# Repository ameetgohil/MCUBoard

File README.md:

# MCUBoard
STM32F104 board with LEDs
<br />
## MCUBoard 3D View

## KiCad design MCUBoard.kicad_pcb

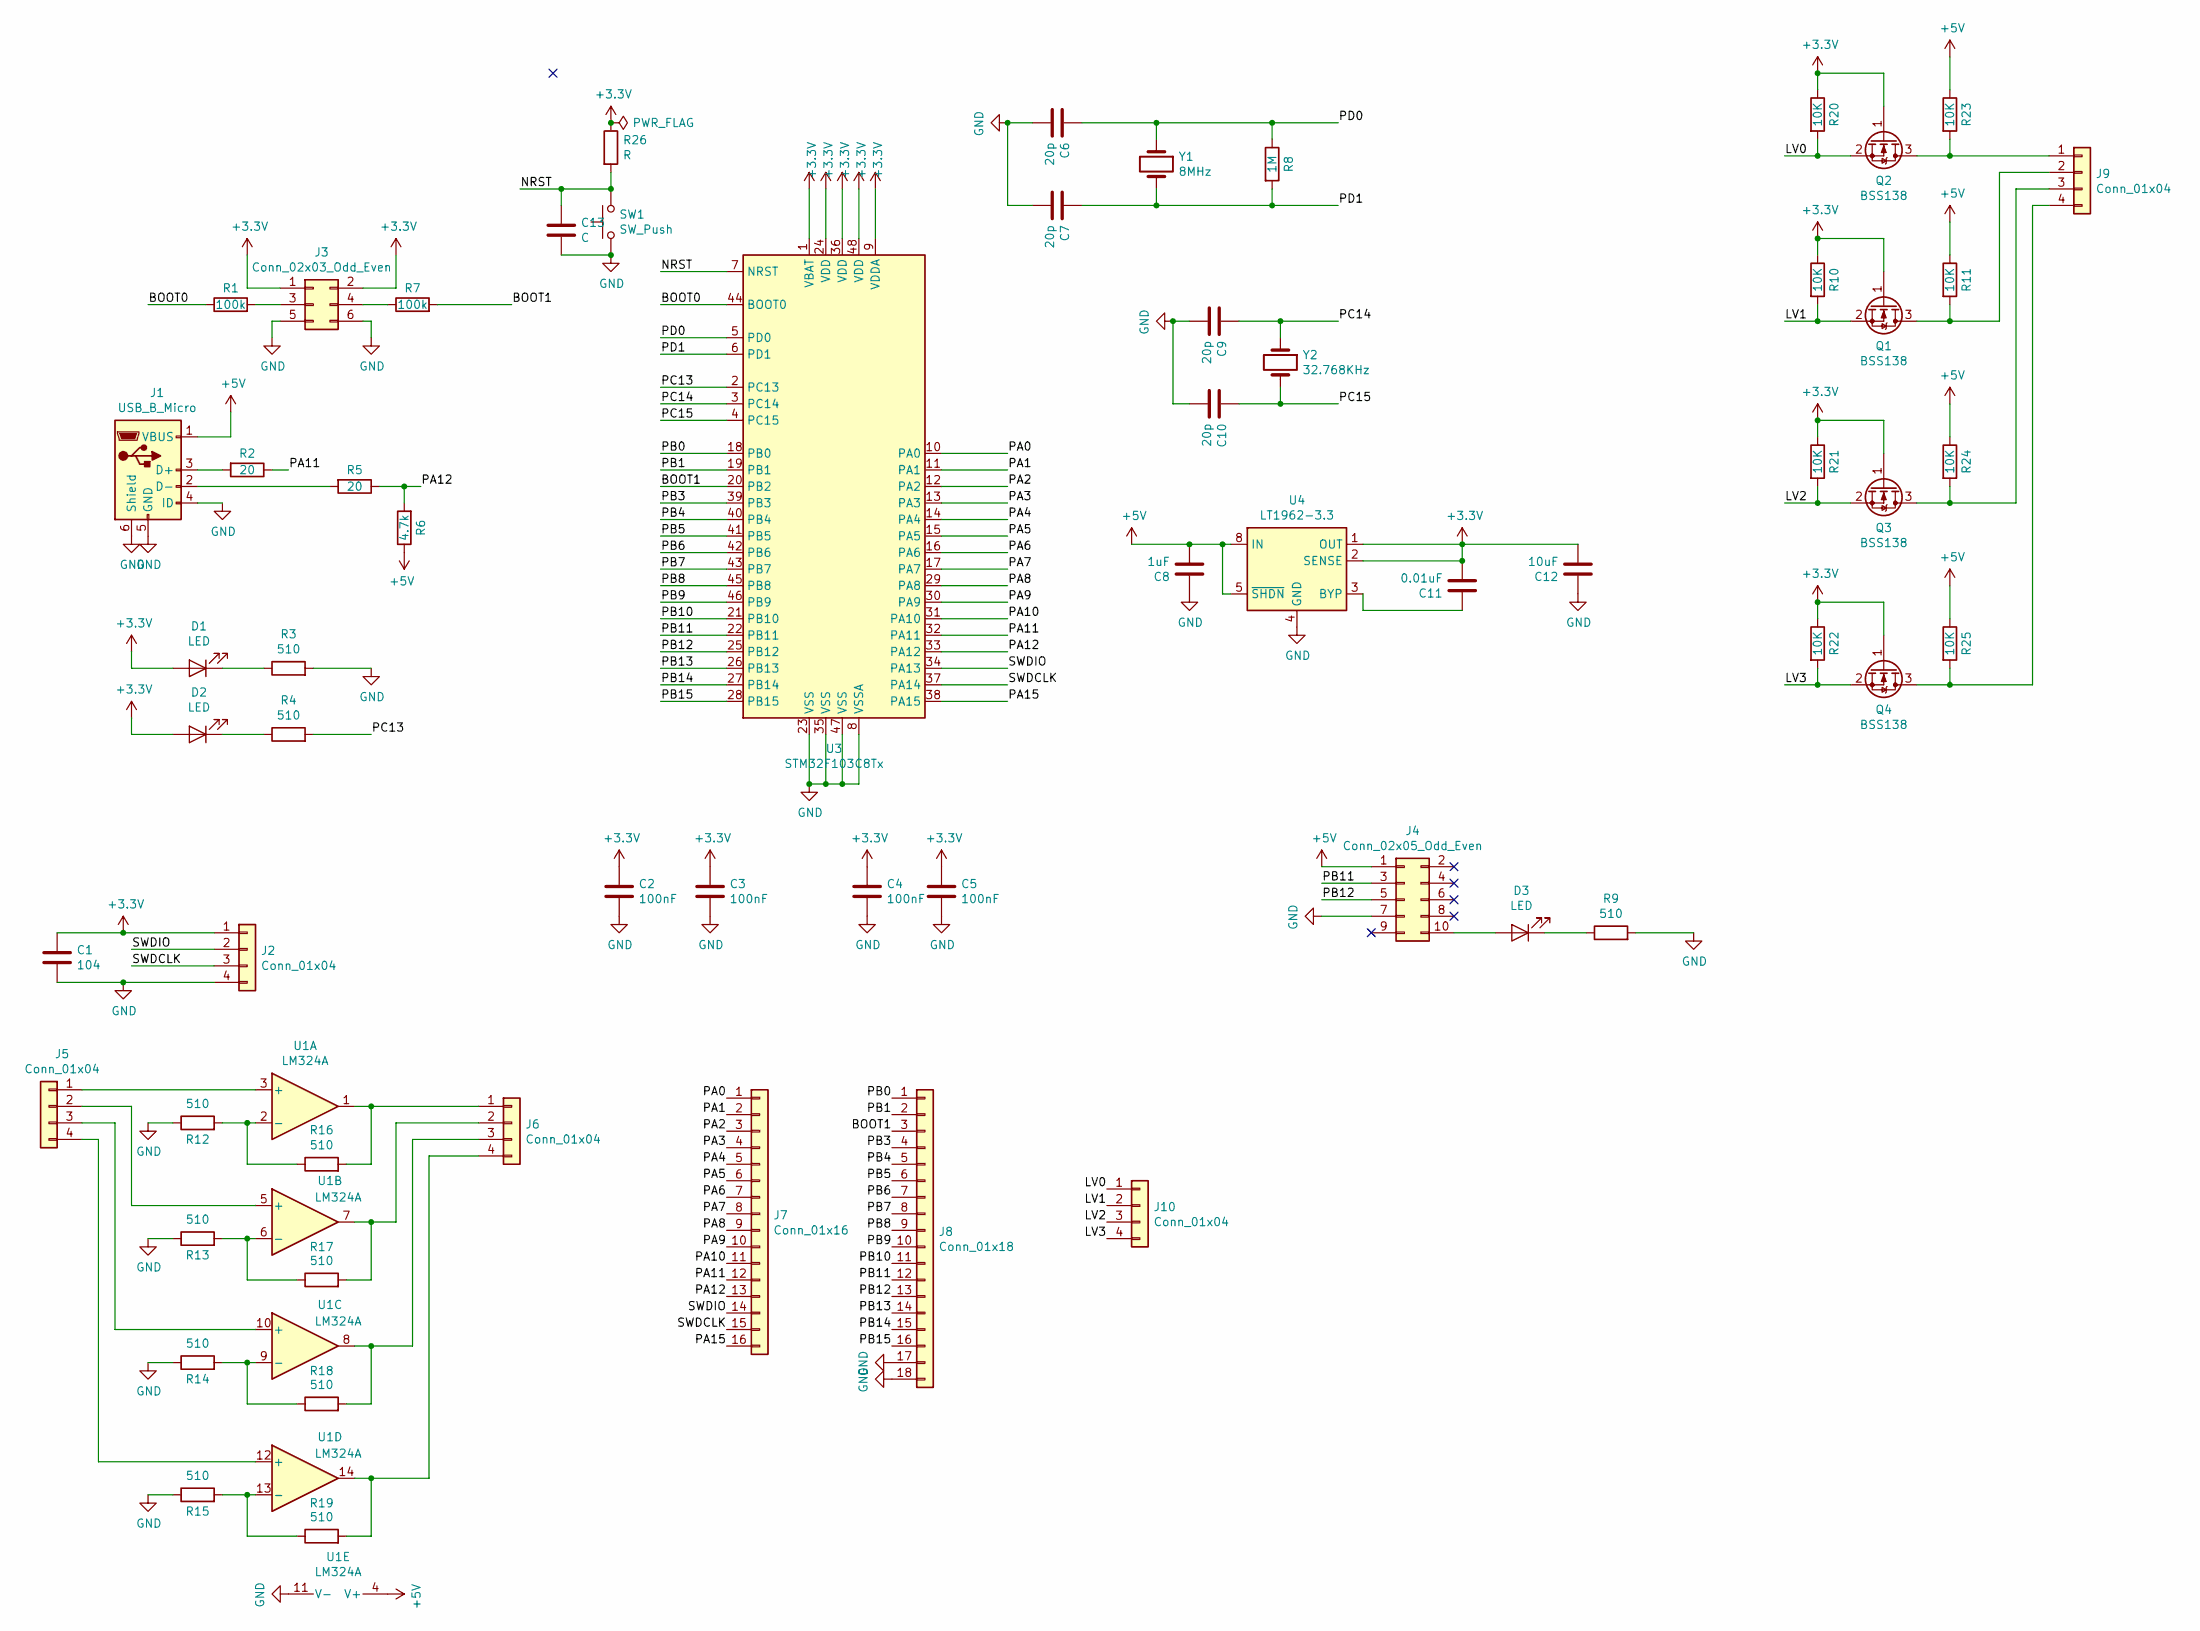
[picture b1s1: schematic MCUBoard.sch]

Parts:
C1: 104; C_1806_4516Metric_Pad1.57x1.80mm_HandSolder
C2, C3, C4, C5: 100nF; C_1806_4516Metric_Pad1.57x1.80mm_HandSolder
C6, C7, C9, C10: 20p; C_1806_4516Metric_Pad1.57x1.80mm_HandSolder
C8: 1uF; C_1806_4516Metric_Pad1.57x1.80mm_HandSolder
C11: 0.01uF; C_1806_4516Metric_Pad1.57x1.80mm_HandSolder
C12: 10uF; C_1806_4516Metric_Pad1.57x1.80mm_HandSolder
C13: C; C_1806_4516Metric_Pad1.57x1.80mm_HandSolder
D1, D2, D3: LED; LED_1206_3216Metric_Pad1.42x1.75mm_HandSolder
J1: USB_B_Micro; USB_Micro-B_Molex_47346-0001
J2, J5, J6, J9, J10: Conn_01x04; PinHeader_1x04_P2.54mm_Vertical
J3: Conn_02x03_Odd_Even; PinHeader_2x03_P2.54mm_Vertical
J4: Conn_02x05_Odd_Even; PinHeader_2x05_P2.54mm_Vertical
J7: Conn_01x16; PinHeader_1x16_P2.54mm_Vertical
J8: Conn_01x18; PinHeader_1x18_P2.54mm_Vertical
Q1, Q2, Q3, Q4: BSS138; SOT-23_Handsoldering
R1, R7: 100k; R_1806_4516Metric_Pad1.57x1.80mm_HandSolder
R2, R5: 20; R_1806_4516Metric_Pad1.57x1.80mm_HandSolder
R3, R4, R9, R12, R13, R14, R15, R16, R17, R18, R19: 510; R_1806_4516Metric_Pad1.57x1.80mm_HandSolder
R6: 4.7k; R_1806_4516Metric_Pad1.57x1.80mm_HandSolder
R8: 1M; R_1806_4516Metric_Pad1.57x1.80mm_HandSolder
R10, R11, R20, R21, R22, R23, R24, R25: 10K; R_1806_4516Metric_Pad1.57x1.80mm_HandSolder
R26: R; R_1806_4516Metric_Pad1.57x1.80mm_HandSolder
SW1: SW_Push; SW_PUSH_6mm
U1: LM324A; LM324-SOIC-14
U3: STM32F103C8Tx; LQFP-48_7x7mm_P0.5mm
U4: LT1962-3.3; MSOP-8_3x3mm_P0.65mm
Y1: 8MHz; Crystal_SMD_0603-2Pin_6.0x3.5mm_HandSoldering
Y2: 32.768KHz; Crystal_SMD_0603-2Pin_6.0x3.5mm_HandSoldering

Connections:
+3V3: C1.1, C2.1, C3.1, C4.1, C5.1, C11.2, C12.2, D1.2 (A), D2.2 (A), J2.1, J3.1, J3.2, Q1.1 (G), Q2.1 (G), Q3.1 (G), Q4.1 (G), R10.1, R20.1, R21.1, R22.1, R26.1, U3.1 (VBAT), U3.9 (VDDA), U3.24 (VDD), U3.36 (VDD), U3.48 (VDD), U4.1 (OUT), U4.2 (SENSE)
+5V: C8.2, J1.1 (VBUS), J4.1, R6.1, R11.1, R23.1, R24.1, R25.1, U1.4 (V+), U4.5 (~SHDN), U4.8 (IN)
/BOOT0: R1.1, U3.44 (BOOT0)
/BOOT1: J8.3, R7.2, U3.20 (PB2)
/LV0: J10.1, Q2.2 (S), R20.2
/LV1: J10.2, Q1.2 (S), R10.2
/LV2: J10.3, Q3.2 (S), R21.2
/LV3: J10.4, Q4.2 (S), R22.2
/NRST: C13.1, R26.2, SW1.2, U3.7 (NRST)
/PA0: J7.1, U3.10 (PA0)
/PA1: J7.2, U3.11 (PA1)
/PA2: J7.3, U3.12 (PA2)
/PA3: J7.4, U3.13 (PA3)
/PA4: J7.5, U3.14 (PA4)
/PA5: J7.6, U3.15 (PA5)
/PA6: J7.7, U3.16 (PA6)
/PA7: J7.8, U3.17 (PA7)
/PA8: J7.9, U3.29 (PA8)
/PA9: J7.10, U3.30 (PA9)
/PA10: J7.11, U3.31 (PA10)
/PA11: J7.12, R2.1, U3.32 (PA11)
/PA12: J7.13, R5.1, R6.2, U3.33 (PA12)
/PA15: J7.16, U3.38 (PA15)
/PB0: J8.1, U3.18 (PB0)
/PB1: J8.2, U3.19 (PB1)
/PB3: J8.4, U3.39 (PB3)
/PB4: J8.5, U3.40 (PB4)
/PB5: J8.6, U3.41 (PB5)
/PB6: J8.7, U3.42 (PB6)
/PB7: J8.8, U3.43 (PB7)
/PB8: J8.9, U3.45 (PB8)
/PB9: J8.10, U3.46 (PB9)
/PB10: J8.11, U3.21 (PB10)
/PB11: J4.3, J8.12, U3.22 (PB11)
/PB12: J4.5, J8.13, U3.25 (PB12)
/PB13: J8.14, U3.26 (PB13)
/PB14: J8.15, U3.27 (PB14)
/PB15: J8.16, U3.28 (PB15)
/PC13: R4.2, U3.2 (PC13)
/PC14: C9.1, U3.3 (PC14), Y2.1
/PC15: C10.1, U3.4 (PC15), Y2.2
/PD0: C6.1, R8.1, U3.5 (PD0), Y1.1
/PD1: C7.1, R8.2, U3.6 (PD1), Y1.2
/SWDCLK: J2.3, J7.15, U3.37 (PA14)
/SWDIO: J2.2, J7.14, U3.34 (PA13)
GND: C1.2, C2.2, C3.2, C4.2, C5.2, C6.2, C7.2, C8.1, C9.2, C10.2, C12.1, C13.2, J1.4 (ID), J1.5 (GND), J1.6 (Shield), J2.4, J3.5, J3.6, J4.7, J8.17, J8.18, R3.2, R9.2, R12.1, R13.1, R14.1, R15.1, SW1.1, U1.11 (V-), U3.8 (VSSA), U3.23 (VSS), U3.35 (VSS), U3.47 (VSS), U4.4 (GND)
unnamed: C11.1, U4.3 (BYP)
unnamed: D1.1 (K), R3.1
unnamed: D2.1 (K), R4.1
unnamed: D3.1 (K), R9.1
unnamed: D3.2 (A), J4.10
unnamed: J1.2 (D-), R5.2
unnamed: J1.3 (D+), R2.2
unnamed: J3.3, R1.2
unnamed: J3.4, R7.1
unnamed: J5.1, U1.3 (+)
unnamed: J5.2, U1.5 (+)
unnamed: J5.3, U1.10 (+)
unnamed: J5.4, U1.12 (+)
unnamed: J6.1, R16.2, U1.1
unnamed: J6.2, R17.2, U1.7
unnamed: J6.3, R18.2, U1.8
unnamed: J6.4, R19.2, U1.14
unnamed: J9.1, Q2.3 (D), R23.2
unnamed: J9.2, Q1.3 (D), R11.2
unnamed: J9.3, Q3.3 (D), R24.2
unnamed: J9.4, Q4.3 (D), R25.2
unnamed: R12.2, R16.1, U1.2 (-)
unnamed: R13.2, R17.1, U1.6 (-)
unnamed: R14.2, R18.1, U1.9 (-)
unnamed: R15.2, R19.1, U1.13 (-)

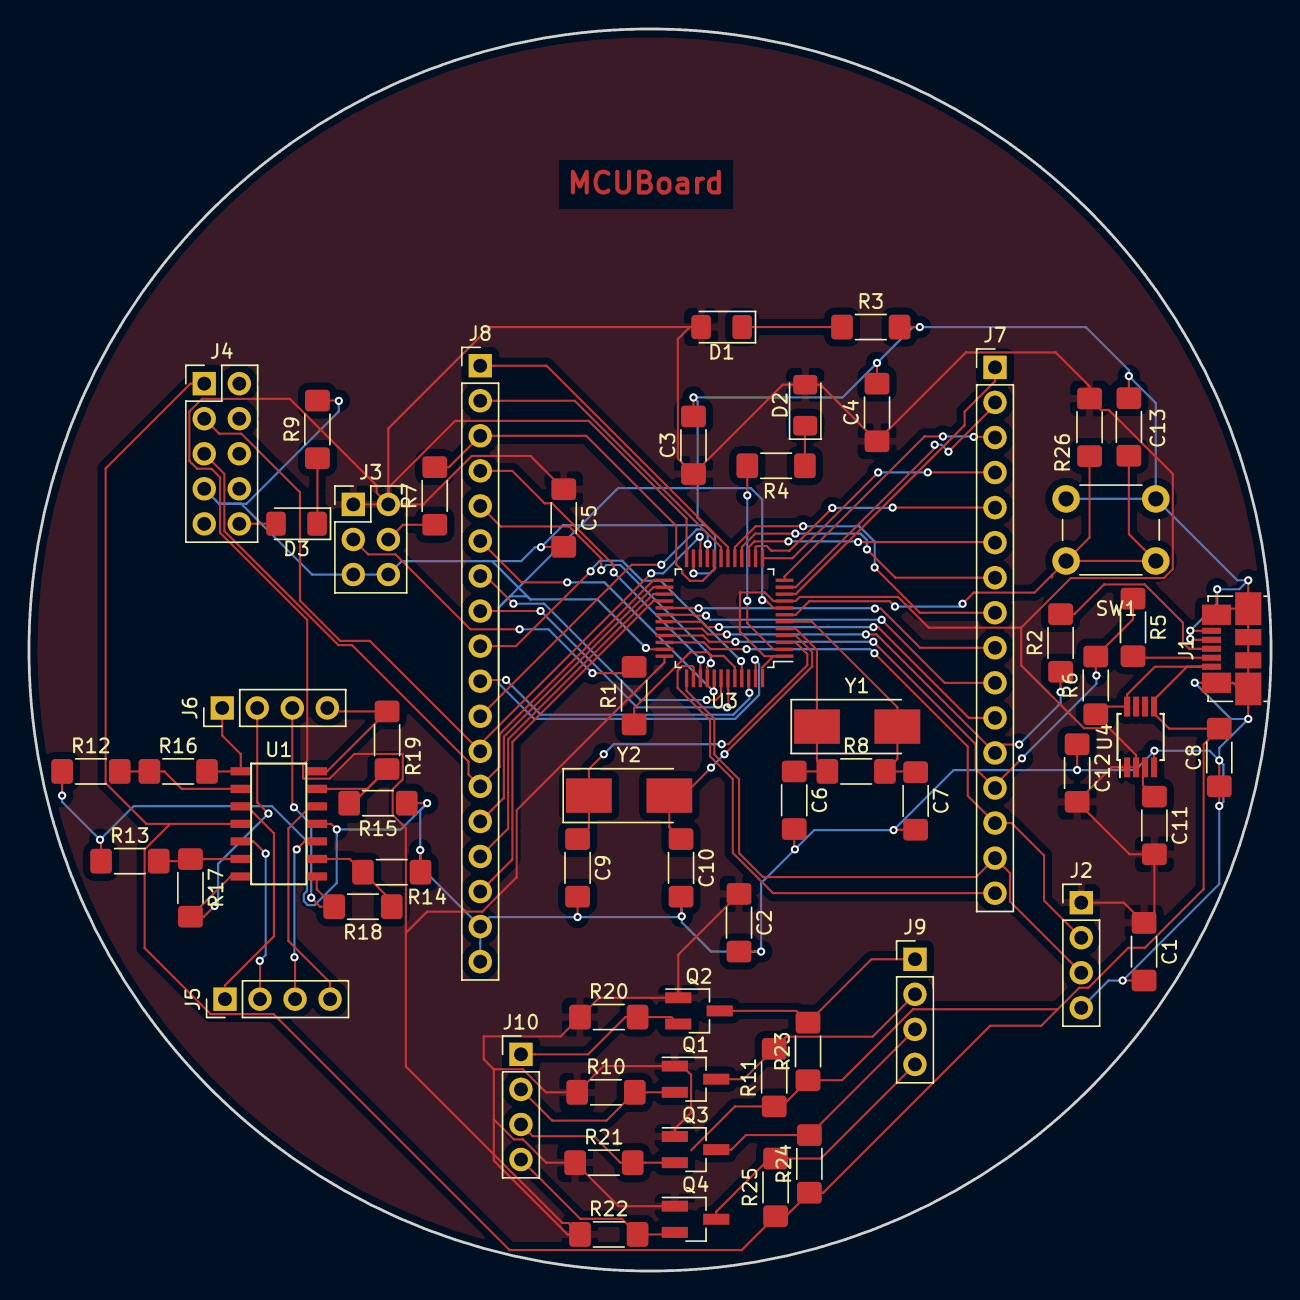
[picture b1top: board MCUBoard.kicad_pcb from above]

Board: 2 copper layers, 90.0 x 90.0 mm, 62 parts (0 on the bottom side), 71 nets.

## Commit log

2018-09-30 inital board schematic
2018-10-01 added LDO to convert 5v to 3.3v
2018-10-01 label mcu and connect power
2018-10-01 added connector for 4D systems uLCD-144-G2
2018-10-12 5V-3.3V bidirectional level shifter
2018-10-16 add opamps
2018-11-16 add jumpers, non-inverting amps
2019-03-08 add power flag, removed all ERC warnings/errors
2019-03-08 create netlist
2019-03-10 add new symbol -to be fixed
2019-03-10 place parts
2019-03-10 change PB headers and route tracks for port B
2019-03-11 route portA and usb
2019-03-11 routing bi-directional level shifters
2019-03-11 route all non-power tracks
2019-03-11 board routed
2019-03-11 copper fill added
2019-03-11 add 3dview image
2019-03-11 better image
